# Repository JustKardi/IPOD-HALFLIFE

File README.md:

# IPOD-HALFLIFE
A simple working iPod

**Overview**

This project was completed for the Hack Club's first week of Half Life. It also includes the materials for week 2, the enclosure. The first part is a PCB. The PCB is powered by an ESP-32 and uses a PCM5011 chip to turn mono audio into high-quality stereo audio. It includes an OLED screen to display songs and menus for navigation. It outputs via a normal 3.5mm audio jack, and it also outputs via Bluetooth (wireless headphones or earbuds). It can accept a microSD for storage and uses USB-C to charge and program the ESP. It features 5 individual buttons in a standard menu navigation layout to perform a variety of actions.

**Process**
1. I started by getting an idea of what to build and what it would look like
2. Make a brief sketch of the final idea
3. I started researching components on LCSC
4. After finalizing components, I put them all on the schematic
5. Wired everything up
6. Position all the elements
7. Auto-route
8. Wrote the firmware

This PCB was designed in EasyEDA STD for Windows. It features many components that are listed below

**Components**
* ESP32-PICO-MINI-02-N8R2 (Microcontroller)
* 10μF Capacitor **x8** (Basic Component)
* 100nF Capacitor **x5** (Basic Component)
* 10μF Capacitor (Basic Component)
* Red LED and Green LED (Basic Component)
* 5.1KΩ Resistor **x2** (Basic Component)
* 100Ω Resistor **x2** (Basic Component)
* 47Ω Resistor (Basic Component)
* 10KΩ Resistor **x11** (Basic Component)
* BUTTON-4X3X2.5 **x7** (Input)
* 100SP1T1B1M1QEH (Input)
* PCM5102APWR (Audio Control)
* PJ-320A-4P DIP (Output)
* TP4056-MS (Battery Control)
* XC6220B331MR-MS (Battery Control)
* HC-TYPE-C-16P-026W (Power Input)
* HS20HS072RX (Display)
* HX TF PUSH (Storage)
* 2KΩ Resistor (Basic Component)

The total materials list with everything is in the BOM

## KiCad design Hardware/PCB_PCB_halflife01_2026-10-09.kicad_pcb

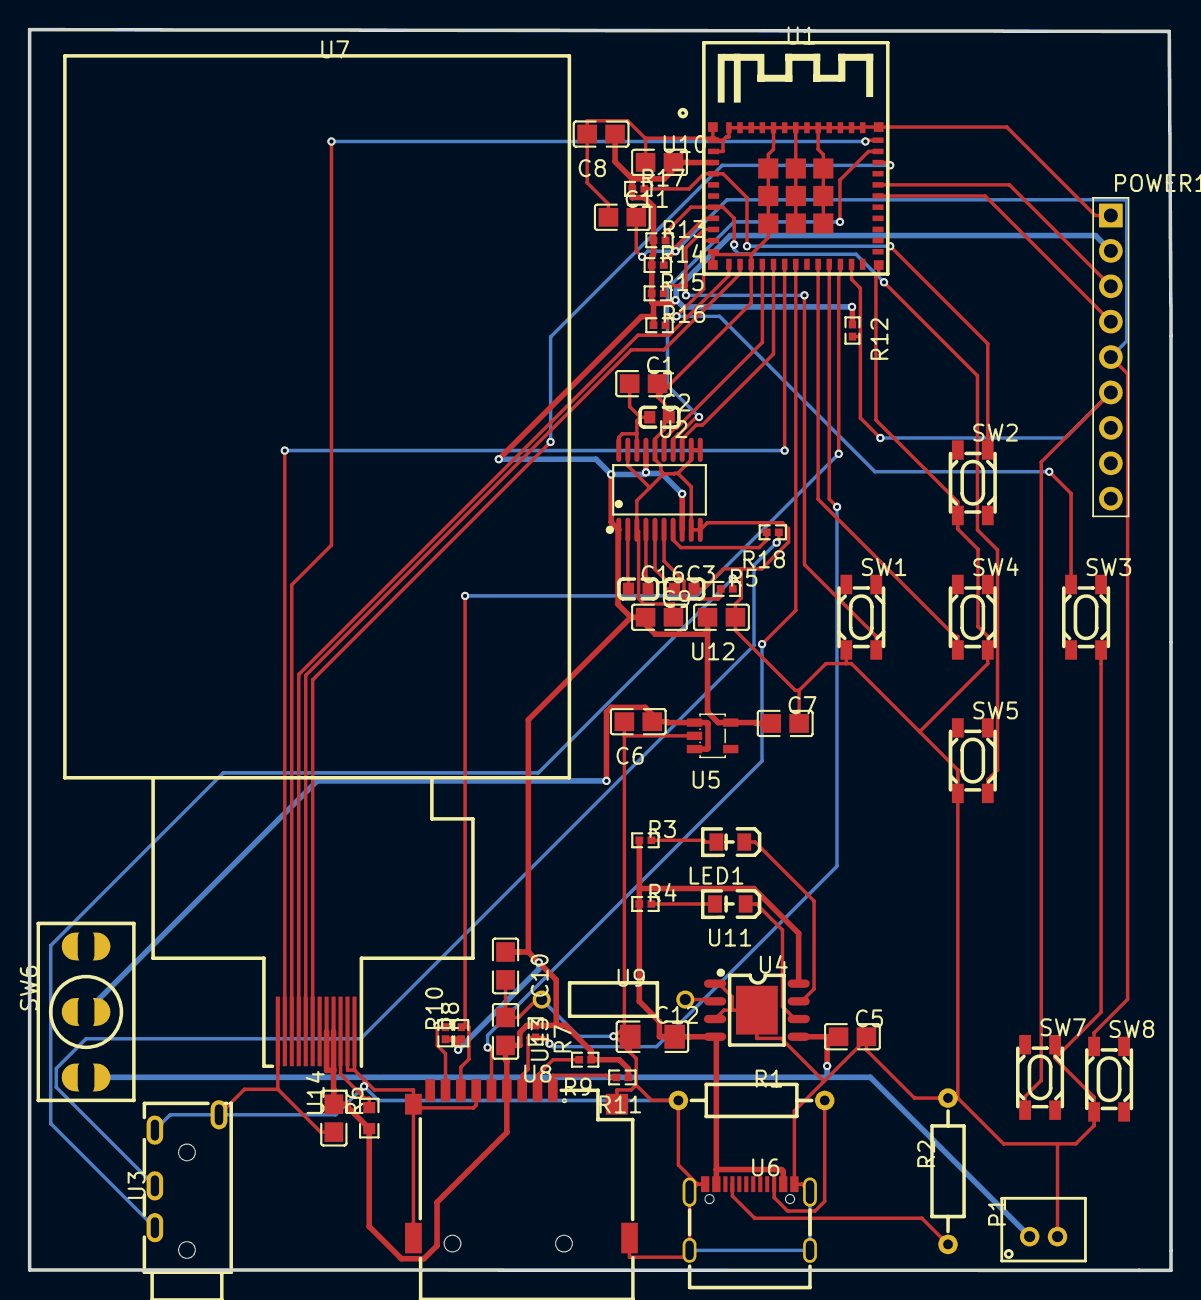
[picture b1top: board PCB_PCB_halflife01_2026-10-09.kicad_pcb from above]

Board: 2 copper layers, 81.9 x 89.0 mm, 55 parts (0 on the bottom side), 44 nets.

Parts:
C1, C5, C6, C7, C8, C9, C10: 10uF; C0805
C2: 100nF; C0603
C3, C16: 2.2uF; C0603
C11: 1uF; C0805
C12: 10uF; C1206
LED1: SMDREDLED红色超高亮0805; LED0805-RD_RED
P1: JST-PH-2-PIN_HEADER; JST-PH-2-PIN 2MM
POWER1: HEADER PAD 6X COPY; PINHEADER_1X09
R1, R2: 5.1kΩ; RES-TH_BD2.3-L6.5-P10.50-D0.5
R3, R4: 1kΩ; R0402
R5, R18: 100Ω; R0402
R6: 47Ω; R0603
R7, R8, R9, R10, R11, R12, R13, R14, R15, R16, R17: 10kΩ; R0402
SW1, SW2, SW3, SW4, SW5, SW7, SW8: BUTTON-4X3X2.5; SW-SMD_4P-L4.2-W3.2-P2.15-LS5.2
SW6: 100SP1T1B1M1QEH; SW-TH_L12.7-W6.9-P4.70_TOGGLESWITCH7102
U1: ESP32-PICO-MINI-02-N8R2; BULETM-SMD_ESP32-PICO-MINI-02-N8R2
U2: PCM5102APWR; TSSOP-20_L6.5-W4.4-P0.65-LS6.4-BL
U3: PJ-320A-4P DIP; AUDIO-TH_PJ-320A-4P-DIP
U4: TP4056-MS; SOP-8_L4.9-W3.9-P1.27-LS6.0-TL-EP
U5: XC6220B331MR-MS; SOT-23-5_L3.0-W1.7-P0.95-LS2.8-BR
U6: HC-TYPE-C-16P-026W; USB-C-SMD_HC-TYPE-C-16P-026W
U7: HS20HS072RX; OLED-SMD_HS20HS072RX
U8: HX TF PUSH; TF-SMD_TF-PUSH
U9: 2kΩ; RES-TH_BD2.4-L6.3-P10.30-D0.6
U10, U12, U13, U14: 100nF; C0805
U11: LED0805-G; LED0805-RD_GREEN

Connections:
3V3: C7.1, C8.1, C9.1, C10.1, POWER1.2, R6.1, R7.1, R8.1, R9.1, R10.1, R11.1, R12.1, R13.1, R14.1, R15.1, R16.1, R17.1, U1.3, U2.1, U2.8, U2.17, U5.5, U7.8, U7.9, U8.4, U10.2, U12.2, U13.2, U14.2
5V: C12.2, R3.1, R4.1, U4.4, U4.8, U6.A4B9, U6.A9B4
GND: C1.2, C2.2, C3.2, C5.2, C6.2, C7.2, C8.2, C9.2, C10.2, C11.1, C12.1, P1.2, POWER1.1, R1.1, R2.2, SW1.4, SW2.4, SW3.2, SW4.2, SW5.4, SW7.1, SW8.4, U1.1, U1.2, U1.11, U1.14, U1.36, U1.37, U1.38, U1.39, U1.40, U1.41, U1.42, U1.43, U1.44, U1.45, U1.46, U1.47, U1.48, U1.49, U1.50, U1.51, U1.52, U1.53, U2.3, U2.9, U2.10, U2.11, U2.12, U2.16, U2.19, U3.A, U3.D, U4.1, U4.3, U4.9, U5.2, U6.12, U6.13, U6.14, U6.15, U6.A1B12, U6.A12B1, U7.1, U7.11, U7.12, U8.6, U8.10, U8.11, U8.12, U8.13, U9.1, U10.1, U12.1, U13.1, U14.1
IO0: POWER1.6, R12.2, SW7.4, U1.23
IO13: SW4.4, U1.20
R3_2: LED1.2, R3.2
U1_4: R17.2, SW2.1, U1.4
U1_7: R13.2, SW5.2, U1.7
U1_8: C11.2, POWER1.5, R14.2, SW8.3, U1.8
U1_9: R15.2, SW1.2, U1.9
U1_10: R16.2, SW3.3, U1.10
U1_12: U1.12, U7.4
U1_13: U1.13, U7.5
U1_15: U1.15, U2.15
U1_16: U1.16, U2.13
U1_17: U1.17, U7.2
U1_18: U1.18, U8.5
U1_21: R7.2, U1.21, U8.3
U1_22: R8.2, U1.22, U8.7
U1_30: POWER1.4, U1.30
U1_31: POWER1.3, U1.31
U1_33: U1.33, U7.6
U1_34: U1.34, U2.14
U1_35: U1.35, U7.3
U2_2: C16.1, U2.2
U2_4: C16.2, U2.4
U2_5: C3.1, U2.5
U2_6: R5.1, U2.6
U2_7: R18.2, U2.7
U2_18: C1.1, C2.1, U2.18, U2.20
U3_B: R5.2, U3.B
U3_C: R18.1, U3.C
U4_2: U4.2, U9.2
U4_6: U4.6, U11.1
U4_7: LED1.1, U4.7
U6_A5: R2.1, U6.A5
U6_B5: R1.2, U6.B5
U7_10: R6.2, U7.10
U8_1: R11.2, U8.1
U8_2: R9.2, U8.2
U8_8: R10.2, U8.8
U11_2: R4.2, U11.2
VBAT: C5.1, P1.1, SW6.1, U4.5
VSW: C6.1, SW6.2, U5.1, U5.3
